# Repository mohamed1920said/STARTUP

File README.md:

# AMR LoRa Irrigation System

Supervised-pilot firmware for three device roles:

- ESP32-S3 central gateway
- TTGO LoRa32 soil sensor node
- TTGO LoRa32 actuator/valve node

The gateway receives AES-128-GCM encrypted LoRa telemetry at 868 MHz, serves a local dashboard, runs guarded irrigation rules and an offline ESP32-S3 Edge-AI advisor, controls actuators, records a versioned AI-ready dataset, and optionally connects to an HTTPS cloud API. Cloud control is CLOSE-only, while local MQTT and browser firmware upload are disabled by default for the supervised pilot.

## Firmware environments

| Environment | Hardware | Purpose |
|---|---|---|
| `central_gateway` | ESP32-S3-DevKitC-1-N8 | Gateway, dashboard, weather and optional cloud bridge |
| `sensor_node` | TTGO LoRa32 v2.1 | Soil moisture, DS18B20 temperature and battery telemetry |
| `actuator_node` | TTGO LoRa32 v2.1 | Fail-safe latching-valve control, verified feedback and hydraulic telemetry |

## Wi-Fi setup

1. Power the central gateway.
2. Read the generated commissioning password from the physical 115200-baud serial console.
3. Connect to the WPA2-protected `STARTUP-Gateway-xxxxxx` Wi-Fi network using that password.
4. Open `http://192.168.4.1`.
5. Select farm Wi-Fi and create an 8–32 character dashboard administrator password.
6. After restart, sign in to the dashboard with username `admin` and the configured password.

Use an isolated pilot network. The dashboard, REST API and WebSocket use HTTP Basic authentication. Gateway firmware updates use physical USB in this build.

LoRa reception, local automation, actuator safety and CSV logging continue when
farm Wi-Fi or internet access is unavailable. Dashboard and cloud access
resume after the gateway can boot on the configured farm network.

## Build

```powershell
pio run -e central_gateway -e sensor_node -e actuator_node
pio run -e central_gateway -t buildfs
```

`platformio.ini` pins Espressif32 platform `7.0.1` and exact tested library versions. Do not loosen those constraints for a pilot image; rebuild and repeat the deployment checklist after any dependency change.

## Upload the ESP32-S3 gateway

```powershell
pio run -e central_gateway -t upload --upload-port COM4
pio run -e central_gateway -t uploadfs --upload-port COM4
```

`flash_central.bat COM4` performs both gateway uploads.

This release changes the gateway partition table. The first installation must
upload both firmware and filesystem; uploading only one will leave the
dashboard or partition layout inconsistent.

## Important protocol rule

Gateway, sensor and actuator firmware must be upgraded together. This revision sends the full 16-byte AES-GCM authentication tag; firmware using the former 4-byte tag cannot communicate with it. ACK is 10 bytes and actuator heartbeat is 17 bytes. Persistent sequence reservations and replay checkpoints are written and read back before use; storage failure suppresses transmission or rejects the command/packet instead of continuing without replay protection.

## Node commissioning

Sensor and actuator images contain no default node ID or PSK. Provision each node over its physical USB serial connection, then add the exact same ID, type and unique 16-byte PSK in the gateway dashboard. Duplicate gateway IDs are refused. Reprovisioning requires explicit removal and a newly generated PSK. An unprovisioned or corrupt node keeps its radio disabled, and gateway OPEN remains blocked until it receives a fresh authenticated packet after provisioning. Never clear or clone the preserved `lora_seq` state while reusing a PSK; generate a new PSK after a full NVS erase.

See the [supervised pilot deployment guide](docs/PILOT_DEPLOYMENT.md) for provisioning commands, cloud endpoints and the required bench and field validation.

## Prototype data collection

The authenticated dashboard's **AI Dataset** panel provides:

- raw and centrally calibrated moisture values;
- UTC epoch time, boot ID, uptime and packet sequence for traceability;
- weather, valve commands, verified valve state, ACKs and optional hydraulics;
- crop, growth-stage and soil metadata per sensor zone;
- field event labels such as rain, leak, blockage and valve fault;
- current and previous CSV downloads.

Configure each sensor's real dry/wet ADC endpoints before collecting training
data. The gateway keeps two rolling 1.25 MiB CSV segments as an outage buffer.
Download both segments regularly or configure the HTTPS cloud connection for a
multi-week dataset. See [AI dataset guide](docs/AI_DATASET.md).

Hydraulic inputs are intentionally disabled by default. Wire and calibrate the
real sensors, then build the actuator with `-DENABLE_HYDRAULIC_SENSORS=1`.

## Edge AI

The central gateway now contains a compact trained model bank for irrigation
need, water/runtime recommendation, rain-delay scheduling, soil dry-down,
watering-effect verification, fault detection and next-day weather prediction.
The dashboard **Edge AI** panel explains each zone recommendation.

AI control is deliberately compiled off with `EDGE_AI_ALLOW_CONTROL=0`. The
model runs in shadow mode while the normal threshold controller and actuator
safety limits remain independent. See [Edge-AI model and deployment guide](docs/EDGE_AI.md).

## Project layout

```text
data/                 Dashboard HTML, JavaScript and CSS
docs/                 Current architecture, wiring and security references
hardware/central_gateway/ KiCad 10 carrier PCB, BOM, clean DRC and fabrication files
lib/                  Required Wi-Fi, dashboard, LoRa protocol and crypto libraries
src/central/          ESP32-S3 gateway firmware
src/sensor/           Soil sensor firmware
src/actuator/         Fail-safe valve actuator firmware
platformio.ini        Three retained PlatformIO environments
partitions_8MB.csv     Gateway OTA + 3.375 MiB LittleFS partition map
flash_central.bat     Windows gateway upload helper
upload_guide.txt      Upload commands and recovery notes
```

## Pilot safety limits

Automatic mode can be enabled only after valid valve feedback received within 90 seconds. Invalid sensor data cancels an automatic OPEN that may still be in flight; invalid or stale data retries CLOSE until fresh feedback verifies commanded and physical state are closed. A failed safety enqueue remains eligible at the next pass without starting its throttle; a normal threshold-driven automatic CLOSE retries after five seconds. Pending tracking rejects duplicate live OPENs and never replaces one to make room. The actuator rejects OPEN below 3400 mV or above an implausible 5000 mV reading; CLOSE remains allowed. OPEN is capped at 300 seconds, the build rejects any higher configured cap, and repeated OPEN commands do not extend the active deadline. Failed OPEN feedback verification immediately sends CLOSE and retries it if necessary.

This does not authorize unattended irrigation. A latching valve needs energy to close, software cannot prove water stopped without independent feedback, and the cloud queue is RAM-only with no automatic CSV backlog replay. Keep a physical master shutoff accessible and complete `docs/PILOT_DEPLOYMENT.md` before any wet pilot.

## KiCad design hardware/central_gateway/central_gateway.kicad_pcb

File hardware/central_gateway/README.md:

# AMR Central Gateway PCB

KiCad 10 carrier board for the AMR central gateway firmware. The board accepts an
ESP32-S3-DevKitC-1-N8R8, adds a soldered RFM95W 868 MHz radio, protected sensor
interfaces, regulated 7-18 V input, an enclosure-button connector, service UART,
and test points.

## Status

- Board revision: `v1.1-prototype`
- Board size: 130 mm x 77 mm, including the ESP32 antenna clearance notch
- Copper layers: 4
- Modular jack footprint: Wuerth Elektronik `615006138421`, manufacturer geometry
- Manufacturing outputs: `manufacturing/central_gateway-fabrication.zip`

The saved DRC result and manufacturing files must be regenerated after every
generator change. This remains a prototype, not a certified production product.
Before sale or outdoor deployment, complete an independent electrical review, RF
tuning, EMC/pre-compliance, surge/EFT/ESD, temperature, and enclosure-ingress tests.

## Physical connector architecture

- J2 is a six-position RJ11-compatible modular jack for the tipping-bucket rain gauge.
- J3 is one six-position RJ11-compatible modular jack for the combined wind cable: wind vane
  plus cup-anemometer reed switch.
- J4 is a three-pin screw terminal for the DHT sensor.
- J5 is a four-pin screw terminal for the BMP280/I2C sensor.
- J6 is a two-pin screw terminal for a passive LDR.
- U2, the RFM95W LoRa module, is soldered directly to the PCB. Its SPI signals are
  intentionally not routed through a screw terminal. J9 is its SMA antenna port.
- The setup/reset button is mounted in the enclosure and wired to J10. There is no
  pushbutton mounted on the PCB.

## Main design choices

- Replaceable ESP32-S3 DevKitC-1 for prototype programming and repair.
- RFM95W-868S2 with a short SMA feed for Tunisia's 868 MHz LoRa deployment.
- 7-18 V input with resettable fuse, SMBJ18A surge clamp, SS34 reverse-polarity
  protection, and R-78E5.0-1.0 5 V regulator.
- AP2112K 3.3 V rail for radio and sensors.
- ESD protection and series resistance on all external sensor signals.
- 100 kOhm / 100 kOhm battery divider matching `WeatherStation.cpp`.
- Dedicated inner ground plane plus bottom ground pour.
- No carrier PCB beneath the ESP32-S3 module antenna.

## Layer stack

| Layer | Use |
|---|---|
| F.Cu | Components, local signals, RF feed |
| In1.Cu | Continuous GND plane |
| In2.Cu | DevKit fan-out and crossing signals |
| B.Cu | Power/signal routing with GND pour |

Order a 1.6 mm, four-layer FR-4 board with at least 1 oz external copper. The
0.45 mm antenna trace is only a prototype starting width. Recalculate the 50 ohm
RF geometry using the fabricator's actual stack-up before production.

## Connector pinout

Pin 1 is the square pad. Modular-jack pin numbers below are PCB contact numbers,
not cable colors; verify the purchased cable continuity before connecting it.

| Connector | PCB pin order | Purpose |
|---|---|---|
| J1 | 1 `VIN_RAW`, 2 `GND` | 7-18 V DC input |
| J2 | 1 NC, 2 NC, 3 `GND`, 4 `RAIN_RAW`, 5 NC, 6 NC | Rain gauge; center pair only |
| J3 | 1 NC, 2 `VANE_RAW`, 3 `GND`, 4 `WIND_RAW`, 5 `GND`, 6 NC | Combined vane + anemometer 6P4C cable |
| J4 | 1 `3V3`, 2 `DHT_RAW`, 3 `GND` | DHT11/DHT22 |
| J5 | 1 `3V3`, 2 `SDA`, 3 `SCL`, 4 `GND` | BMP280 / I2C sensor |
| J6 | 1 `LDR_RAW`, 2 `GND` | Passive LDR; PCB provides 10 kOhm pull-up |
| J7 | 1 `BAT+`, 2 `GND` | 0-6.0 V measurement input only |
| J8 | 1 `3V3`, 2 `GND`, 3 `UART_TX`, 4 `UART_RX` | 3.3 V service UART |
| J9 | center RF, shell `GND` | SMA for tuned 868 MHz antenna |
| J10 | 1 `SETUP_RESET`, 2 `GND` | Enclosure-mounted normally-open button |

Do not power the system through J7 and never apply more than 6.0 V to it. J8 is
3.3 V logic and is not 5 V tolerant. Never apply external voltage to J10: the
panel button must only short pins 1 and 2.

## Weather-kit electrical behavior

- Rain: each bucket tip closes the reed switch and represents 0.2794 mm.
- Wind speed: one closure per second represents approximately 2.4 km/h, or
  0.667 m/s.
- Wind direction: the vane exposes a 16-position resistor network. The firmware
  lookup is calculated for the PCB's 3.3 V, 10 kOhm pull-up; verify and calibrate
  the ADC centers on assembled production hardware.

## Firmware-to-board map

| Function | ESP32-S3 GPIO | PCB net |
|---|---:|---|
| LoRa NSS | 18 | `LORA_NSS` |
| LoRa DIO0 | 2 | `LORA_DIO0` |
| LoRa reset | 14 | `LORA_RST` |
| LoRa SCK / MOSI / MISO | 12 / 11 / 13 | `LORA_SCK` / `LORA_MOSI` / `LORA_MISO` |
| Rain | 6 | `RAIN_GPIO` |
| Wind pulse | 3 | `WIND_GPIO` |
| Wind vane ADC | 10 | `VANE_ADC` |
| DHT data | 7 | `DHT_GPIO` |
| LDR ADC | 9 | `LDR_ADC` |
| Battery ADC | 8 | `BATT_ADC` |
| I2C SDA / SCL | 4 / 5 | `I2C_SDA_GPIO` / `I2C_SCL_GPIO` |
| Wi-Fi setup reset | 0 | `SETUP_RESET` |

Hold the enclosure button for five seconds to request the Wi-Fi setup reset.
GPIO0 is also a boot-strapping pin, so do not hold the button while applying
power or resetting the DevKit unless firmware-download mode is intended.

## Assembly and verification

- TP1: +5 V
- TP2: +3.3 V peripheral rail
- TP3: GND
- TP4: LoRa DIO1

Before fitting U1 or U2, power the carrier from a current-limited bench supply and
verify TP1 and TP2. Fit the ESP32 module, then fit the RFM95W and connect its
antenna before transmitting. Continuity-test both weather cables to confirm their
contact order before plugging them into J2/J3.

Observe diode polarity. D1 cathode connects to `VIN_FUSED`; D2 anode connects to
`VIN_FUSED` and cathode to `VIN_PROTECTED`. For D3-D10, confirm the purchased
part's polarity and marking against the schematic and datasheet.

## Regeneration and verification

From the repository root:

```powershell
python hardware\central_gateway\generate_kicad.py
& 'C:\Program Files\KiCad\10.0\bin\kicad-cli.exe' pcb upgrade hardware\central_gateway\central_gateway.kicad_pcb
& 'C:\Program Files\KiCad\10.0\bin\kicad-cli.exe' pcb drc --refill-zones --save-board --severity-all --format report --output hardware\central_gateway\central_gateway-drc.rpt hardware\central_gateway\central_gateway.kicad_pcb
```

The routed PCB and deterministic generator are authoritative. The legacy
schematic is a compact circuit-review reference and is converted by KiCad on
first open.

## Production checklist

1. Verify the exact DevKit, Wuerth jacks, screw terminals, JST header, and panel
   button against purchased samples and the final enclosure.
2. Confirm cable pinout and add keying/labels so rain and wind plugs cannot be
   exchanged in the field.
3. Tune RF geometry for the chosen stack-up and test the installed antenna/VNA
   performance inside the final enclosure.
4. Validate regulator temperature and brownout margin at maximum Wi-Fi/LoRa load.
5. Test all external ports for the required IEC ESD, EFT, and surge environment.
6. Use a UV-resistant IP65/IP67 enclosure, strain relief, suitable glands or
   sealed panel couplers, conformal coating where appropriate, and fused power.
7. Run a pilot build and production functional-test fixture before volume manufacture.

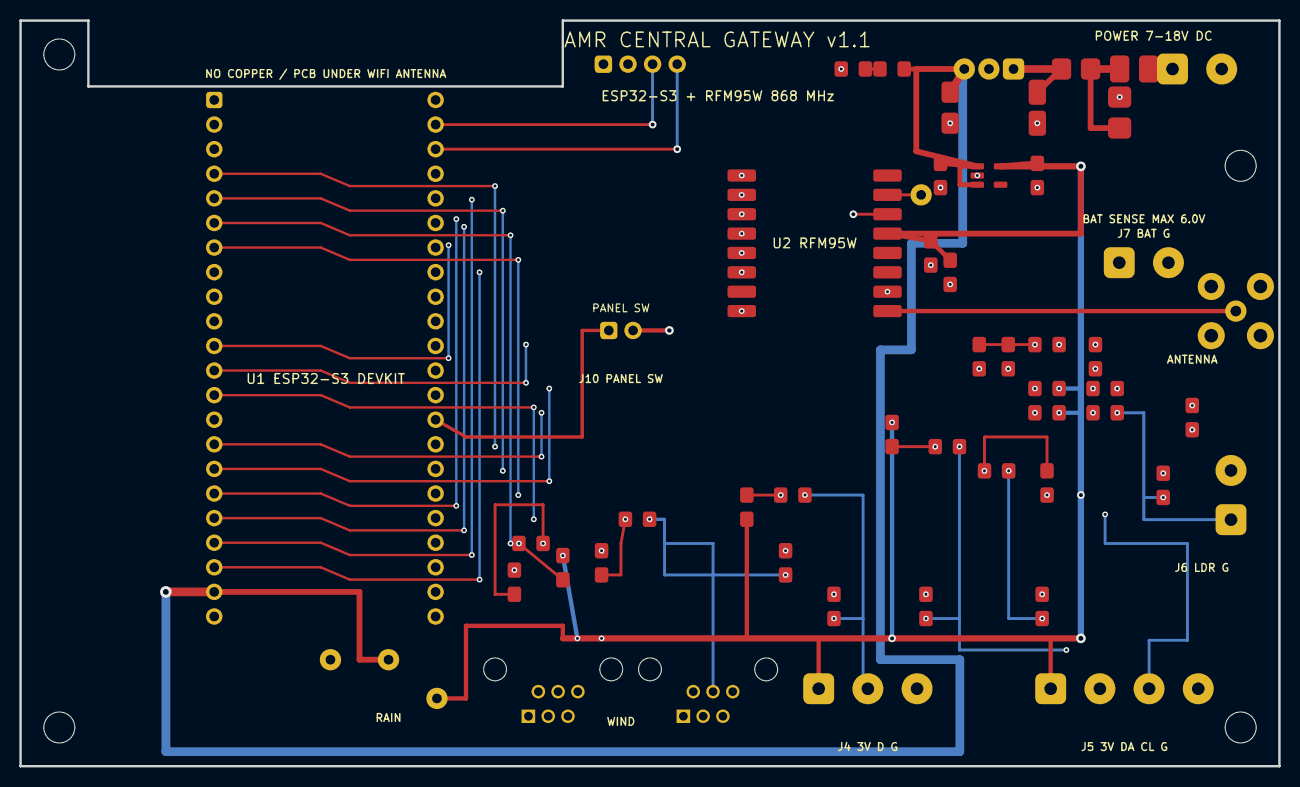
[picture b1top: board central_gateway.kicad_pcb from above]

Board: 4 copper layers, 130.0 x 77.0 mm, 58 parts (0 on the bottom side), 34 nets.

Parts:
C1: 10uF 35V; AMR_Central_C_1210
C2: 22uF 10V; AMR_Central_C_1206
C3, C4: 1uF; AMR_Central_C_0805
C5: 10uF; AMR_Central_C_0805
C6, C11: 100nF; AMR_Central_C_0805
D1: SMBJ18A; AMR_Central_D_SMB
D2: SS34; AMR_Central_D_SMA
D3, D4, D5, D6, D7, D8, D9: PESD3V3; AMR_Central_D_SOD323
D10: BZT52C6V2; AMR_Central_D_SOD323
F1: PTC 0.75A; AMR_Central_Fuse_1812
H1, H2, H3, H4: M3; AMR_Central_MountingHole_3.2mm
J1: POWER 7-18V DC; AMR_Central_TerminalBlock_2
J2: RAIN RJ11; AMR_Central_WR-MJ_615006138421
J3: WIND+VANE RJ11; AMR_Central_WR-MJ_615006138421
J4: DHT11; AMR_Central_TerminalBlock_3
J5: BMP280 I2C; AMR_Central_TerminalBlock_4
J6: PASSIVE LDR; AMR_Central_TerminalBlock_2
J7: BAT SENSE 0-6V; AMR_Central_TerminalBlock_2
J8: SERVICE UART; AMR_Central_Header_1x4
J9: SMA_868MHz; AMR_Central_SMA_Vertical_THT
J10: PANEL SETUP BUTTON; AMR_Central_JST_XH_B2B-XH-A_1x02_P2.50mm
LED1: GREEN; AMR_Central_LED_0805
R1, R2, R4, R12, R14: 1k; AMR_Central_R_0805
R3, R5, R13, R15: 10k; AMR_Central_R_0805
R6: 220R; AMR_Central_R_0805
R7, R10, R11: 4.7k; AMR_Central_R_0805
R8, R9: 100R; AMR_Central_R_0805
R16, R17: 100k 1%; AMR_Central_R_0805
TP1: +5V; AMR_Central_TestPoint_THT
TP2: +3V3; AMR_Central_TestPoint_THT
TP3: GND; AMR_Central_TestPoint_THT
TP4: LORA_DIO1; AMR_Central_TestPoint_THT
U1: ESP32-S3-DevKitC-1-N8R8; AMR_Central_ESP32-S3-DevKitC-1_Carrier
U2: RFM95W-868S2; AMR_Central_HOPERF_RFM95W_SMD
U3: R-78E5.0-1.0; AMR_Central_RECOM_R-78E5.0-1.0_SIP3
U4: AP2112K-3.3; AMR_Central_SOT-23-5

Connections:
+3V3_PERIPH: C4.2, C5.2, C6.2, J4.1, J5.1, J8.1, R3.2, R5.2, R7.1, R10.2, R11.1, R13.2, R15.2, TP2.1, U2.13 (3V3), U4.5 (VOUT)
+5V: C2.2, C3.2, R1.2, TP1.1, U1.21 (5V), U3.3 (VOUT), U4.1 (VIN), U4.3 (EN)
BATT_ADC: C11.2, R16.1, R17.2, U1.12 (GPIO8)
BATT_SENSE_RAW: D10.1, J7.1, R16.2
DHT_GPIO: R6.1, R7.2, U1.7 (GPIO7)
DHT_RAW: D5.1, J4.2, R6.2
GND: C1.1, C2.1, C3.1, C4.1, C5.1, C6.1, C11.1, D1.2, D3.2, D4.2, D5.2, D6.2, D7.2, D8.2, D9.2, D10.2, J1.2, J2.3, J3.3, J3.5, J4.3, J5.4, J6.2, J7.2, J8.2, J9.2, J9.3, J9.4, J9.5, J10.2, LED1.1, R17.1, TP3.1, U1.22 (GND), U1.23 (GND), U1.24 (GND), U1.44 (GND), U2.1 (GND), U2.8 (GND), U2.10 (GND), U3.2 (GND), U4.2 (GND)
I2C_SCL_GPIO: R9.1, R11.2, U1.5 (GPIO5)
I2C_SCL_RAW: D7.1, J5.3, R9.2
I2C_SDA_GPIO: R8.1, R10.1, U1.4 (GPIO4)
I2C_SDA_RAW: D6.1, J5.2, R8.2
LDR_ADC: R14.1, R15.1, U1.15 (GPIO9)
LDR_RAW: D9.1, J6.1, R14.2
LORA_ANT: J9.1, U2.9 (ANT)
LORA_DIO0: U1.40 (GPIO2), U2.14 (DIO0)
LORA_DIO1: TP4.1, U2.15 (DIO1)
LORA_MISO: U1.19 (GPIO13), U2.2 (MISO)
LORA_MOSI: U1.17 (GPIO11), U2.3 (MOSI)
LORA_NSS: U1.11 (GPIO18), U2.5 (NSS)
LORA_RST: U1.20 (GPIO14), U2.6 (RESET)
LORA_SCK: U1.18 (GPIO12), U2.4 (SCK)
PWR_LED_A: LED1.2, R1.1
RAIN_GPIO: R2.1, R3.1, U1.6 (GPIO6)
RAIN_RAW: D3.1, J2.4, R2.2
SETUP_RESET: J10.1, U1.31 (GPIO0)
UART_RX: J8.4, U1.42 (GPIO44)
UART_TX: J8.3, U1.43 (GPIO43)
VANE_ADC: R12.1, R13.1, U1.16 (GPIO10)
VANE_RAW: D8.1, J3.2, R12.2
VIN_FUSED: D1.1, D2.2, F1.1
VIN_PROTECTED: C1.2, D2.1, U3.1 (VIN)
VIN_RAW: F1.2, J1.1
WIND_GPIO: R4.1, R5.1, U1.13 (GPIO3)
WIND_RAW: D4.1, J3.4, R4.2

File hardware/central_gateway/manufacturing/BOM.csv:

Reference,Value,Description,Manufacturer Part Number,Footprint,Quantity
U1,ESP32-S3-DevKitC-1-N8R8,Espressif ESP32-S3 development board,ESP32-S3-DEVKITC-1-N8R8,AMR_Central_ESP32-S3-DevKitC-1_Carrier,1
U2,RFM95W-868S2,HopeRF 868/915MHz LoRa module,RFM95W-868S2,AMR_Central_HOPERF_RFM95W_SMD,1
U3,R-78E5.0-1.0,1A 5V SIP switching regulator,R-78E5.0-1.0,AMR_Central_RECOM_R-78E5.0-1.0_SIP3,1
U4,AP2112K-3.3,600mA low-noise 3.3V LDO,AP2112K-3.3TRG1,AMR_Central_SOT-23-5,1
"J1,J6,J7",2-pin 5.08mm terminal block,Pluggable or fixed terminal block,Generic,AMR_Central_TerminalBlock_2,3
"J2,J3",615006138421,"Horizontal six-position RJ11-compatible modular jack, tab up",Wuerth Elektronik 615006138421,AMR_Central_WR-MJ_615006138421,2
J4,3-pin 5.08mm terminal block,Pluggable or fixed terminal block,Generic,AMR_Central_TerminalBlock_3,1
J5,4-pin 5.08mm terminal block,Pluggable or fixed terminal block,Generic,AMR_Central_TerminalBlock_4,1
J8,1x4 2.54mm header,Service UART header,Generic,AMR_Central_Header_1x4,1
J9,SMA female vertical,868MHz antenna connector,Generic,AMR_Central_SMA_Vertical_THT,1
J10,B2B-XH-A(LF)(SN),2-pin 2.50mm locking header for enclosure button harness,JST B2B-XH-A(LF)(SN),AMR_Central_JST_XH_B2B-XH-A_1x02_P2.50mm,1
ENC-SW1,Panel momentary NO button,Enclosure-mounted setup/reset button wired to J10,Select for enclosure/IP rating,OFF_BOARD,1
F1,PTC 0.75A,1812 resettable fuse,MF-MSMF075-2,AMR_Central_Fuse_1812,1
D1,SMBJ18A,600W unidirectional TVS,SMBJ18A,AMR_Central_D_SMB,1
D2,SS34,3A 40V Schottky diode,SS34,AMR_Central_D_SMA,1
D3-D9,PESD3V3,3.3V ESD protection diode,PESD3V3U1BA,AMR_Central_D_SOD323,7
D10,BZT52C6V2,6.2V Zener clamp,BZT52C6V2,AMR_Central_D_SOD323,1
LED1,GREEN,0805 green LED,Generic,AMR_Central_LED_0805,1
"R1,R2,R4,R12,R14",1k,0805 1% resistor,Generic,AMR_Central_R_0805,5
"R3,R5,R13,R15",10k,0805 1% resistor,Generic,AMR_Central_R_0805,4
R6,220R,0805 1% resistor,Generic,AMR_Central_R_0805,1
"R7,R10,R11",4.7k,0805 1% resistor,Generic,AMR_Central_R_0805,3
"R8,R9",100R,0805 1% resistor,Generic,AMR_Central_R_0805,2
"R16,R17",100k 1%,0805 precision divider,Generic,AMR_Central_R_0805,2
C1,10uF 35V,1210 X7R input capacitor,Generic,AMR_Central_C_1210,1
C2,22uF 10V,1206 X7R output capacitor,Generic,AMR_Central_C_1206,1
"C3,C4",1uF,0805 X7R capacitor,Generic,AMR_Central_C_0805,2
C5,10uF,0805 X7R LoRa bulk capacitor,Generic,AMR_Central_C_0805,1
"C6,C11",100nF,0805 X7R capacitor,Generic,AMR_Central_C_0805,2
TP1-TP4,Test points,Through-hole loop/test point,Generic,AMR_Central_TestPoint_THT,4

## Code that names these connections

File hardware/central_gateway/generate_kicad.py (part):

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NET_NAMES = [
    "GND", "+5V", "+3V3_PERIPH", "VIN_RAW", "VIN_FUSED", "VIN_PROTECTED",
    "LORA_NSS", "LORA_DIO0", "LORA_RST", "LORA_SCK", "LORA_MOSI", "LORA_MISO",
    "LORA_ANT", "LORA_DIO1", "RAIN_GPIO", "RAIN_RAW", "WIND_GPIO", "WIND_RAW",
    "DHT_GPIO", "DHT_RAW", "I2C_SDA_GPIO", "I2C_SDA_RAW", "I2C_SCL_GPIO",
    "I2C_SCL_RAW", "VANE_ADC", "VANE_RAW", "LDR_ADC", "LDR_RAW", "BATT_ADC",
    "BATT_SENSE_RAW", "SETUP_RESET", "UART_TX", "UART_RX", "PWR_LED_A",
]
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        # Global pad numbering follows the accepted KiCad footprint proposal:
        # J1 = pads 1..22 top-to-bottom; J3 = pads 44..23 top-to-bottom.
        names = {
            1: "3V3", 2: "3V3", 3: "EN", 4: "GPIO4", 5: "GPIO5", 6: "GPIO6",
            7: "GPIO7", 8: "GPIO15", 9: "GPIO16", 10: "GPIO17", 11: "GPIO18",
            12: "GPIO8", 13: "GPIO3", 14: "GPIO46", 15: "GPIO9", 16: "GPIO10",
            17: "GPIO11", 18: "GPIO12", 19: "GPIO13", 20: "GPIO14", 21: "5V",
            22: "GND", 23: "GND", 24: "GND", 25: "GPIO47", 26: "GPIO48",
            27: "GPIO45", 28: "GPIO0", 29: "GPIO35", 30: "GPIO36", 31: "GPIO37",
            32: "GPIO38", 33: "GPIO39", 34: "GPIO40", 35: "GPIO41", 36: "GPIO42",
            37: "GPIO2", 38: "GPIO1", 39: "GPIO44", 40: "GPIO43", 41: "GND",
            42: "GND", 43: "GND", 44: "GND",
        }
        # Correct the global-number mapping for the J3 header.
        names.update({
            44: "GND", 43: "GPIO43", 42: "GPIO44", 41: "GPIO1", 40: "GPIO2",
            39: "GPIO42", 38: "GPIO41", 37: "GPIO40", 36: "GPIO39", 35: "GPIO38",
            34: "GPIO37", 33: "GPIO36", 32: "GPIO35", 31: "GPIO0", 30: "GPIO45",
            29: "GPIO48", 28: "GPIO47", 27: "GPIO21", 26: "GPIO20", 25: "GPIO19",
            24: "GND", 23: "GND",
        })
        pad_nets: dict[int, str | None] = {
            4: "I2C_SDA_GPIO", 5: "I2C_SCL_GPIO", 6: "RAIN_GPIO", 7: "DHT_GPIO",
            11: "LORA_NSS", 12: "BATT_ADC", 13: "WIND_GPIO", 15: "LDR_ADC",
            16: "VANE_ADC", 17: "LORA_MOSI", 18: "LORA_SCK", 19: "LORA_MISO",
            20: "LORA_RST", 21: "+5V", 22: "GND", 23: "GND", 24: "GND",
            31: "SETUP_RESET", 40: "LORA_DIO0", 42: "UART_RX", 43: "UART_TX",
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
    def add_dcdc(self, at: tuple[float, float]) -> None:
        ref = "U3"
        pins = [("1", (2.54, 0), "VIN_PROTECTED", "VIN"), ("2", (0, 0), "GND", "GND"),
                ("3", (-2.54, 0), "+5V", "VOUT")]
        pads = []
        for number, local, net, function in pins:
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                  spacing=3.2, angle=90, pad_size=(2.4, 2.2), body=(4.2, 2.2), footprint="D_SMB")
    b.add_two_pad("D2", "SS34", (129.0, 31.0), ("VIN_PROTECTED", "VIN_FUSED"),
                  spacing=3.0, pad_size=(2.0, 2.2), body=(3.8, 2.1), footprint="D_SMA")
    b.add_two_pad("C1", "10uF 35V", (125.0, 35.0), ("GND", "VIN_PROTECTED"), angle=90,
                  spacing=3.2, pad_size=(1.8, 2.6), body=(3.2, 2.5), footprint="C_1210")
    b.add_two_pad("C2", "22uF 10V", (116.0, 35.0), ("GND", "+5V"), angle=90,
                  spacing=3.2, pad_size=(1.8, 2.2), body=(3.2, 1.8), footprint="C_1206")
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    b.add_panel_button_connector((82.0, 58.0))

    # Rain input conditioning.
    b.add_two_pad("R2", "1k", (72.71, 80.00), ("RAIN_GPIO", "RAIN_RAW"), footprint="R_0805")
    b.add_two_pad("R3", "10k", (76.0, 82.5), ("RAIN_GPIO", "+3V3_PERIPH"), angle=90, footprint="R_0805")
    b.add_two_pad("D3", "PESD3V3", (71.0, 84.00), ("RAIN_RAW", "GND"), angle=90, footprint="D_SOD323")

    # Wind input conditioning.
    b.add_two_pad("R4", "1k", (83.71, 77.50), ("WIND_GPIO", "WIND_RAW"), footprint="R_0805")
    b.add_two_pad("R5", "10k", (80.0, 82.0), ("WIND_GPIO", "+3V3_PERIPH"), angle=90, footprint="R_0805")
    b.add_two_pad("D4", "PESD3V3", (99.0, 82.00), ("WIND_RAW", "GND"), angle=90, footprint="D_SOD323")

    # DHT digital input.
    b.add_two_pad("R6", "220R", (99.75, 75.00), ("DHT_GPIO", "DHT_RAW"), footprint="R_0805")
    b.add_two_pad("R7", "4.7k", (95.0, 76.25), ("+3V3_PERIPH", "DHT_GPIO"), angle=90, footprint="R_0805")
    b.add_two_pad("D5", "PESD3V3", (104.0, 86.50), ("DHT_RAW", "GND"), angle=90, footprint="D_SOD323")

    # I2C filtering, pull-ups and ESD.
    b.add_two_pad("R8", "100R", (115.71, 70.00), ("I2C_SDA_GPIO", "I2C_SDA_RAW"), footprint="R_0805")
    b.add_two_pad("R9", "100R", (120.79, 72.50), ("I2C_SCL_GPIO", "I2C_SCL_RAW"), footprint="R_0805")
    b.add_two_pad("R10", "4.7k", (110.0, 68.75), ("I2C_SDA_GPIO", "+3V3_PERIPH"), angle=90, footprint="R_0805")
    b.add_two_pad("R11", "4.7k", (126.0, 73.75), ("+3V3_PERIPH", "I2C_SCL_GPIO"), angle=90, footprint="R_0805")
    b.add_two_pad("D6", "PESD3V3", (113.5, 86.50), ("I2C_SDA_RAW", "GND"), angle=90, footprint="D_SOD323")
    b.add_two_pad("D7", "PESD3V3", (125.5, 86.50), ("I2C_SCL_RAW", "GND"), angle=90, footprint="D_SOD323")

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    ):
        b.route_devkit_left(net, b.pad("U1", source_pad), b.pad("U2", target_pad), lane,
                            tag=net, transition_y=transition_y)
    # GPIO2/DIO0 runs below the ground plane route layer and enters the SMD pad from inside.
    dio0_start = b.pad("U1", 40)
    dio0_end = b.pad("U2", 14)
    b.route_poly("LORA_DIO0", [dio0_start, (70.0, 38.0), (106.0, 38.0), (106.0, 46.0)],
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
    # Weather signal routes from the exact GPIO pads to the protected interface circuits.
    signal_routes = [
        ("I2C_SDA_GPIO", 4, "R8", 1, 69.0), ("I2C_SCL_GPIO", 5, "R9", 1, 69.8),
        ("RAIN_GPIO", 6, "R2", 1, 70.6), ("DHT_GPIO", 7, "R6", 1, 71.4),
        ("BATT_ADC", 12, "R16", 1, 72.2), ("WIND_GPIO", 13, "R4", 1, 73.0),
        ("LDR_ADC", 15, "R15", 1, 73.8), ("VANE_ADC", 16, "R13", 1, 74.6),
    ]
    for net, source_pad, target_ref, target_pad, lane in signal_routes:
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                               (86.5, b.pad(series, 2)[1]), b.pad(series, 2)],
                         0.30, "B.Cu", prefix + "-esd")

    straight("DHT_GPIO", "R7", 2, "R6", 1, "dht-gpio")
    raw_to_connector("DHT_RAW", "R6", "J4", 2, "dht-raw",
                     [(107.0, b.pad("R6", 2)[1]), (107.0, b.pad("J4", 2)[1])])
    b.add_via("DHT_RAW", b.pad("D5", 1), size=0.60, drill=0.30, tag="dht-esd-via")
    b.add_segment("DHT_RAW", b.pad("D5", 1),
                  (107.0, b.pad("D5", 1)[1]), 0.30, "B.Cu", "dht-esd")

    straight("I2C_SDA_GPIO", "R10", 1, "R8", 1, "sda-gpio")
    sda_target = b.pad("J5", 2)
    sda_source = b.pad("R8", 2)
    b.add_via("I2C_SDA_RAW", sda_source, size=0.60, drill=0.30, tag="sda-raw-via")
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    b.add_via("I2C_SDA_RAW", b.pad("D6", 1), size=0.60, drill=0.30, tag="sda-esd-via")
    b.add_segment("I2C_SDA_RAW", b.pad("D6", 1), (b.pad("R8", 2)[0], b.pad("D6", 1)[1]),
                  0.30, "B.Cu", "sda-esd")
    b.route_poly("I2C_SCL_GPIO", [b.pad("R9", 1), (b.pad("R9", 1)[0], 69.0),
                                   (b.pad("R11", 2)[0], 69.0), b.pad("R11", 2)],
                 0.30, "F.Cu", "scl-gpio")
    scl_source, scl_target = b.pad("R9", 2), b.pad("J5", 3)
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    parts.append(symbol("TESTPOINT", "TP", [("TP", "1", -200, 0, "R", "P")]))

    # DevKit symbol mirrors the PCB pad numbering.
    left_names = ["3V3", "3V3", "EN", "GPIO4", "GPIO5", "GPIO6", "GPIO7", "GPIO15",
                  "GPIO16", "GPIO17", "GPIO18", "GPIO8", "GPIO3", "GPIO46", "GPIO9",
                  "GPIO10", "GPIO11", "GPIO12", "GPIO13", "GPIO14", "5V", "GND"]
    right_names = ["GND", "GPIO43", "GPIO44", "GPIO1", "GPIO2", "GPIO42", "GPIO41", "GPIO40",
                   "GPIO39", "GPIO38", "GPIO37", "GPIO36", "GPIO35", "GPIO0", "GPIO45", "GPIO48",
                   "GPIO47", "GPIO21", "GPIO20", "GPIO19", "GND", "GND"]
    pins = []
    for index, pname in enumerate(left_names):
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    # Controller and radio.
    blocks.append(component("ESP32_S3_DEVKITC_1", "U1", "ESP32-S3-DevKitC-1-N8R8",
                            "AMR_Central:ESP32-S3-DevKitC-1_Carrier", 3000, 3800))
    left_labels = {4:"I2C_SDA_GPIO",5:"I2C_SCL_GPIO",6:"RAIN_GPIO",7:"DHT_GPIO",11:"LORA_NSS",
                   12:"BATT_ADC",13:"WIND_GPIO",15:"LDR_ADC",16:"VANE_ADC",17:"LORA_MOSI",
                   18:"LORA_SCK",19:"LORA_MISO",20:"LORA_RST",21:"+5V",22:"GND"}
    right_labels = {44:"GND",43:"UART_TX",42:"UART_RX",40:"LORA_DIO0",31:"SETUP_RESET",24:"GND",23:"GND"}
    for number in range(1, 23):
        x, y = 2100, 2750 + (number - 1) * 100
        blocks.append(text_label(x, y, left_labels[number]) if number in left_labels else no_connect(x, y))
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        x, y = 6900, 3050 + index * 100
        blocks.append(text_label(x, y, rfm_right[number], 2) if number in rfm_right else no_connect(x, y))
    blocks.append(component("SMA", "J9", "SMA 868MHz", "AMR_Central:SMA_Vertical_THT", 7800, 3800))
    blocks += [text_label(7500, 3700, "LORA_ANT"), text_label(7500, 3900, "GND")]

    # Power chain.
    blocks.append("Text Notes 5100 900 0    70   ~ 12\nPROTECTED FIELD POWER")
    blocks.append(component("CONN_1X2", "J1", "POWER 7-18V DC", "AMR_Central:TerminalBlock_2", 5200, 1300))
    blocks += [text_label(4900, 1225, "VIN_RAW"), text_label(4900, 1375, "GND")]
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
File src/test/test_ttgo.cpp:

#include <SPI.h>
#include <LoRa.h>

#define LORA_CS 18
#define LORA_IRQ 26
#define LORA_RST 14
#define LORA_SCK 5
#define LORA_MISO 19
#define LORA_MOSI 27

volatile int rxLen = 0;

void onRx(int len) {
  rxLen = len;
}

void setup() {
  Serial.begin(115200); delay(500);
  SPI.begin(LORA_SCK, LORA_MISO, LORA_MOSI, LORA_CS);
  LoRa.setPins(LORA_CS, LORA_RST, LORA_IRQ);
  int st = LoRa.begin(868E6);
  Serial.printf("LoRa begin: %d\n", st);
  LoRa.setSpreadingFactor(9);
  LoRa.setSignalBandwidth(125E3);
  LoRa.setCodingRate4(5);
  LoRa.setSyncWord(0x12);
  LoRa.setTxPower(10);
  LoRa.onReceive(onRx);
  LoRa.receive();
  Serial.println("Ready - LoRa lib listening...");
}

uint32_t last = 0;
void loop() {
  if (rxLen) {
    int len = rxLen; rxLen = 0;
    uint8_t buf[64];
    int i = 0;
    while (LoRa.available() && i < 64) buf[i++] = LoRa.read();
    Serial.printf("Rx! len=%d (%d read) rssi=%d snr=%.1f\n", len, i, LoRa.packetRssi(), LoRa.packetSnr());
    for (int j = 0; j < i; j++) Serial.printf("%02X", buf[j]);
    Serial.println();
    LoRa.receive();
  }
  uint32_t now = millis();
  if (now - last >= 10000) {
    last = now;
    Serial.printf("tick %u\n", now/1000);
  }
}
